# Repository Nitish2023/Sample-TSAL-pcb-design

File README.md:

# pcb-designs
I am using Kicad for making pcb designs
# gerber file.zip
contains the gerber file of the pcb
# intro.wrl 
contains 3D model 
# intro.step
contains pcb design

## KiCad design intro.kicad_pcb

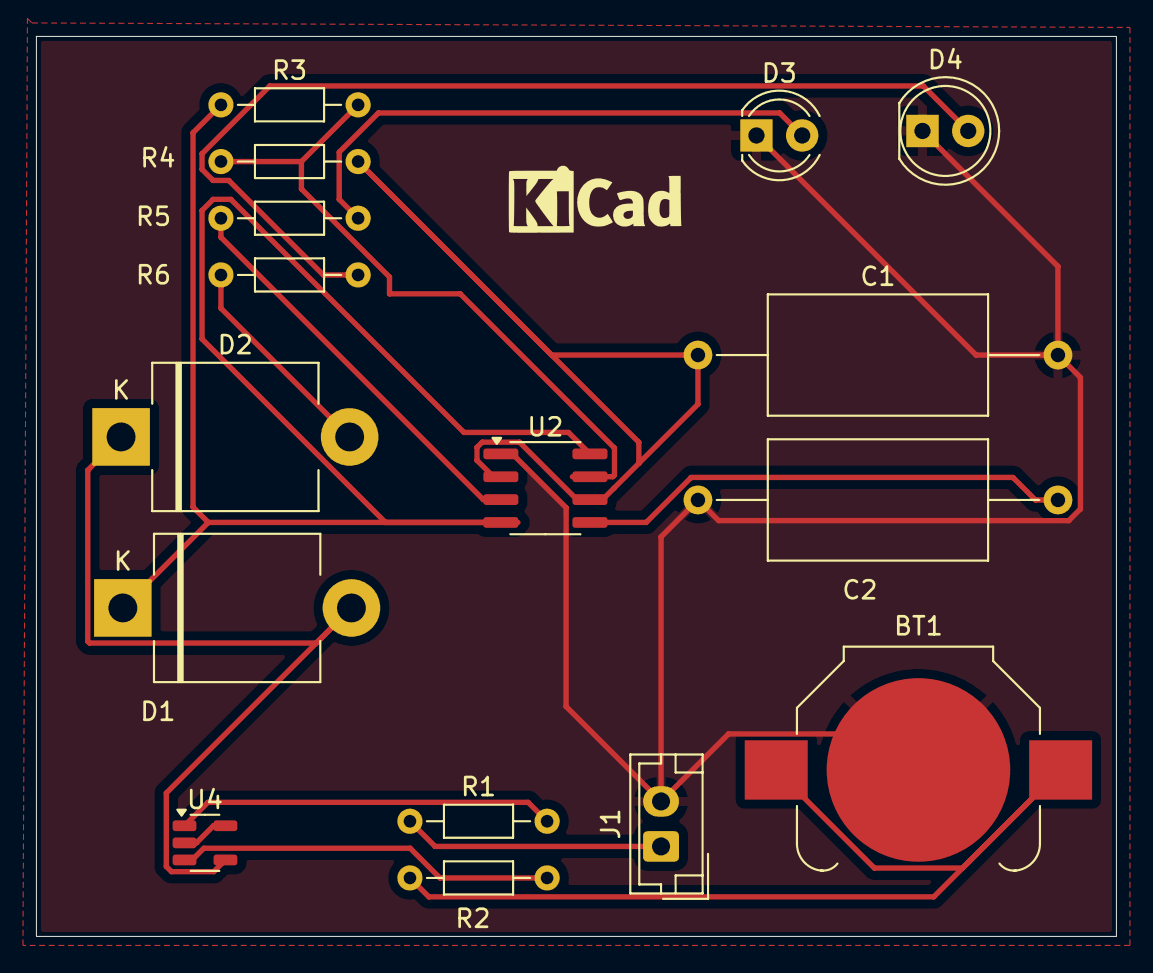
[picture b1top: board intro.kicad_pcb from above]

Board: 2 copper layers, 60.0 x 50.0 mm, 16 parts (0 on the bottom side), 15 nets.

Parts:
BT1: Battery_Cell; BatteryHolder_Keystone_3000_1x12mm
C1, C2: C; C_Axial_L12.0mm_D6.5mm_P20.00mm_Horizontal
D1, D2: D; D_5KPW_P12.70mm_Horizontal
D3: LED; LED_D4.0mm
D4: LED; LED_D5.0mm
J1: Conn_01x02_Socket; JST_EH_B2B-EH-A_1x02_P2.50mm_Vertical
R1, R2, R3, R4, R5, R6: R; R_Axial_DIN0204_L3.6mm_D1.6mm_P7.62mm_Horizontal
U2: ICM7555xB; SOIC-8_3.9x4.9mm_P1.27mm
U4: LM397; SOT-23-5

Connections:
+12V: U4.2 (V-), U4.5 (V+)
GND: BT1.2 (-), C1.2, C2.1, D3.1 (K), D4.1 (K), J1.2, U2.1 (GND)
unnamed: BT1.1 (+), R2.1
unnamed: D1.2 (A), D2.1 (K), U4.4
unnamed: D1.1 (K), R3.1, U2.4 (R), U2.8 (VCC)
unnamed: D2.2 (A), R6.1
unnamed: D3.2 (A), R5.2
unnamed: D4.2 (A), R6.2
unnamed: J1.1, R1.1
unnamed: C2.2, U2.5 (CV)
unnamed: R3.2, R4.1, U2.7 (DIS)
unnamed: R5.1, U2.3 (Q)
unnamed: C1.1, R4.2, U2.2 (TR), U2.6 (THR)
unnamed: R2.2, U4.3 (+)
unnamed: R1.2, U4.1 (-)

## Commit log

2024-07-10 Create Sample TSAL pcb
2024-12-10 Rename Screenshot 2024-12-10 210047.png to Front
2024-12-10 Rename Screenshot 2024-12-10 210638.png to Back
2024-12-10 Rename Screenshot 2024-12-10 210856.png to Schematic
2025-10-19 Update and rename intro.kicad_pcb to pcb
2025-10-19 Update and rename intro.kicad_sch to schematic
2025-10-19 Rename pcb 2 [Autosaved].pdsprj to Proteus_Simulation.pdsprj
